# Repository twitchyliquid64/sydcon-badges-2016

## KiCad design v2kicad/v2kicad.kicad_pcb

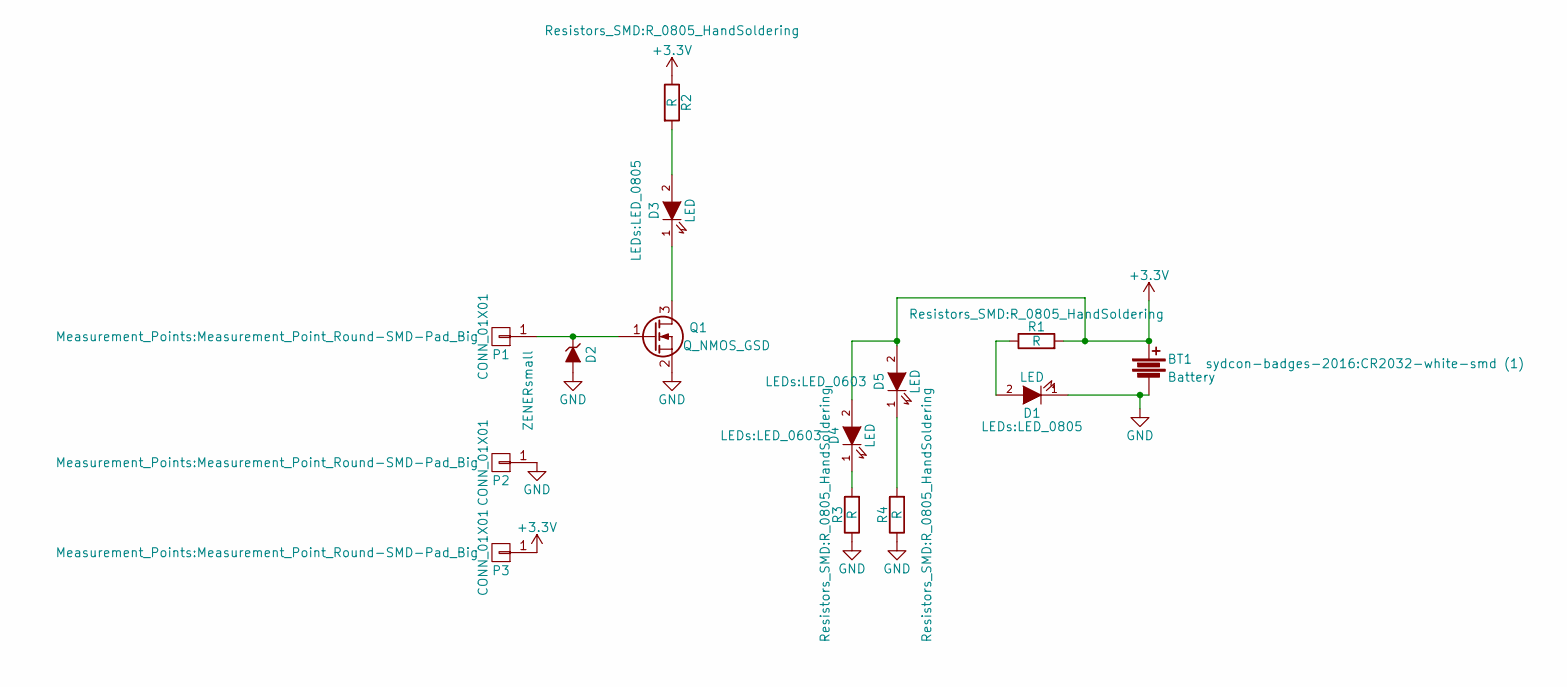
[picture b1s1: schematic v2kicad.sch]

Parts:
BT1: Battery; CR2032-white-smd (1)
D1, D3: LED; LED_0805
D2: ZENERsmall; SMA-SMB_Universal_Handsoldering
D4, D5: LED; LED_0603
P1, P2, P3: CONN_01X01; Measurement_Point_Round-SMD-Pad_Big
Q1: Q_NMOS_GSD; SOT-23_Handsoldering
R1, R2, R3, R4: R; R_0805_HandSoldering

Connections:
+3V3: BT1.1, D4.2 (A), D5.2 (A), P3.1, R1.2, R2.1
GND: BT1.2, D1.1 (K), D2.2 (A), P2.1, Q1.2 (S), R3.1, R4.1
unnamed: D1.2 (A), R1.1
unnamed: D2.1 (K), P1.1, Q1.1 (G)
unnamed: D3.1 (K), Q1.3 (D)
unnamed: D3.2 (A), R2.2
unnamed: D4.1 (K), R3.2
unnamed: D5.1 (K), R4.2

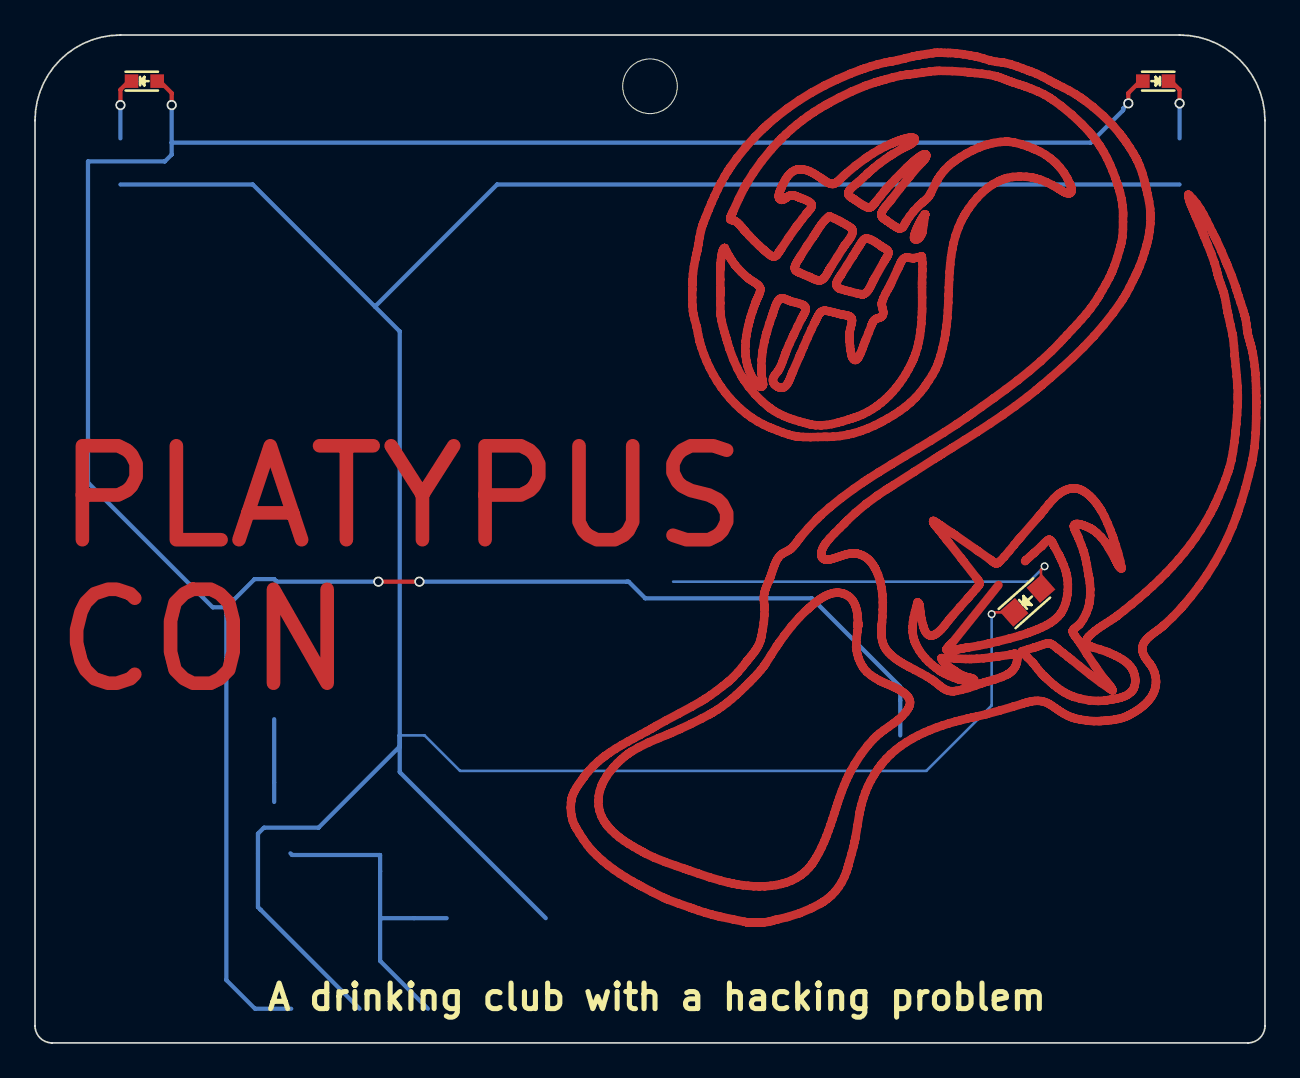
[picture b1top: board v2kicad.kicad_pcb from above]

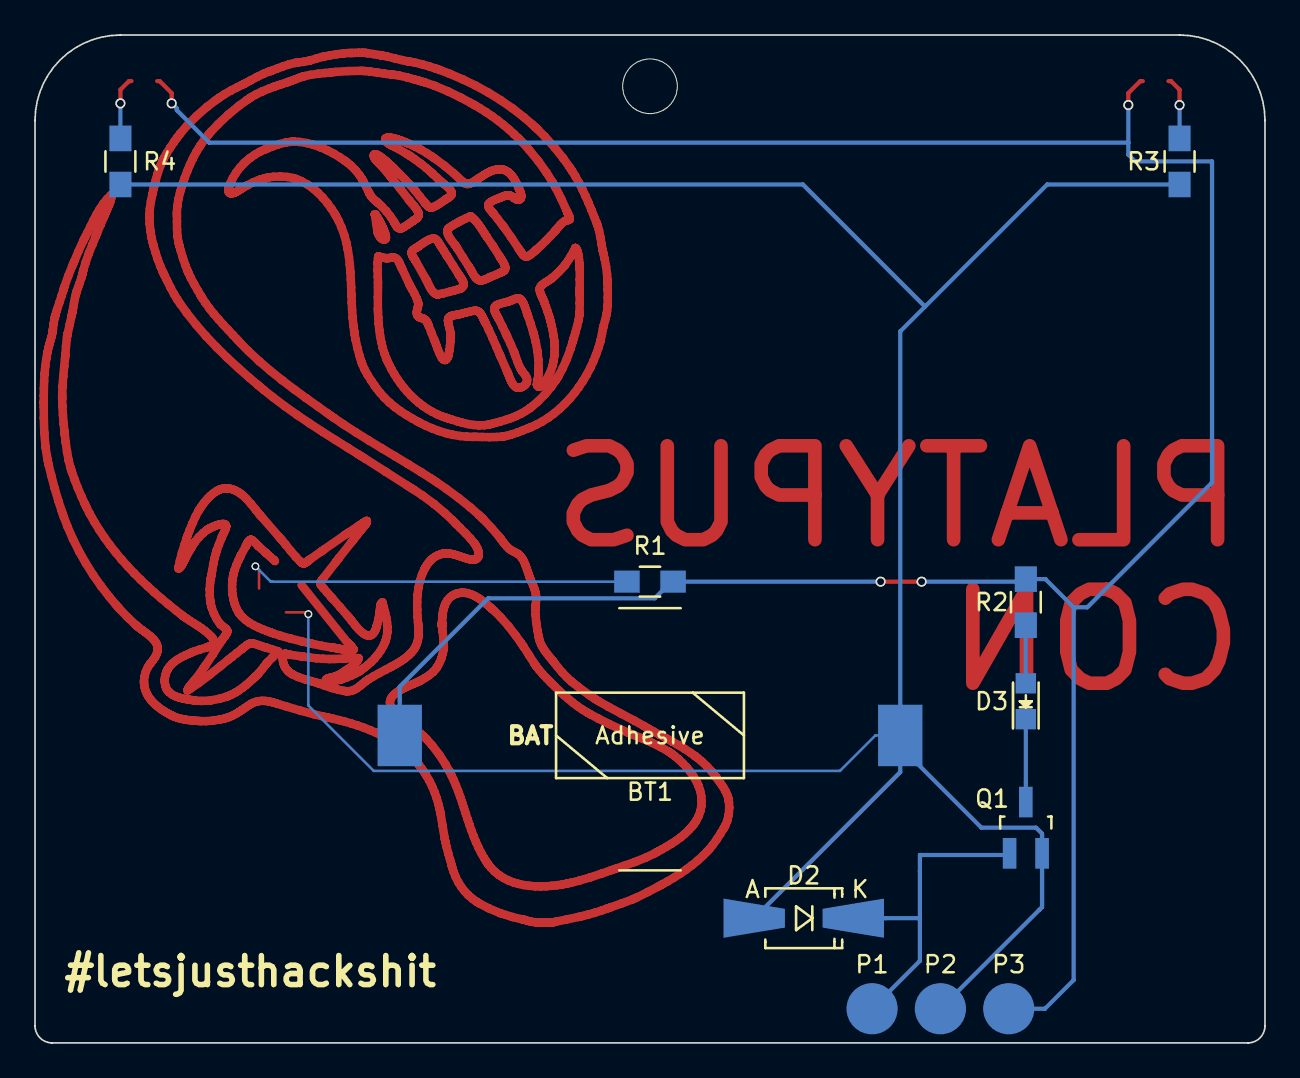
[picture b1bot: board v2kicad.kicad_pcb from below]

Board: 2 copper layers, 72.0 x 59.0 mm, 14 parts (11 on the bottom side), 8 nets.

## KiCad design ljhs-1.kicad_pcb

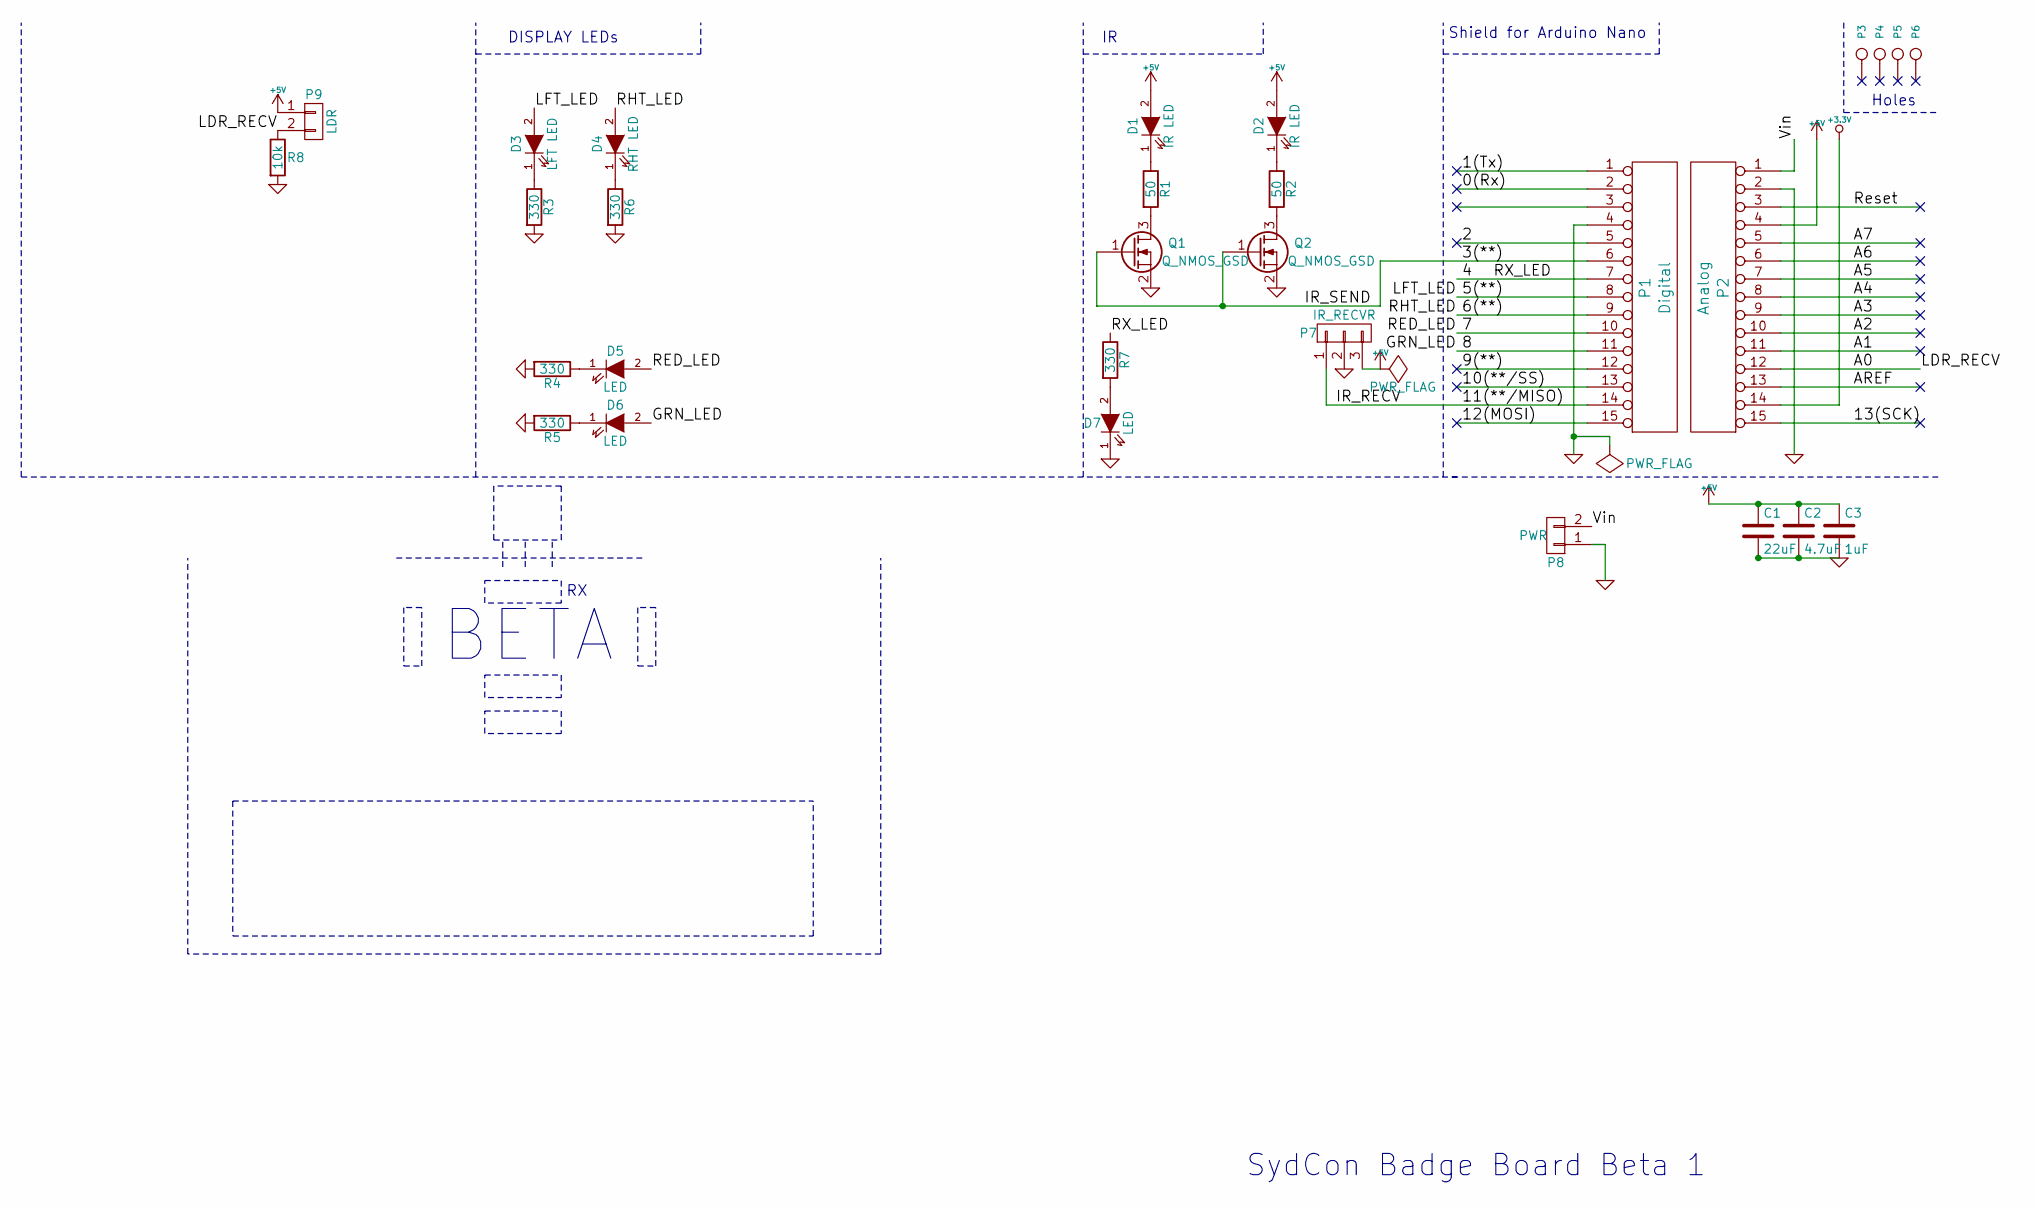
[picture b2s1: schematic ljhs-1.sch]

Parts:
C1: 22uF; C_0805_HandSoldering
C2: 4.7uF; C_0805_HandSoldering
C3: 1uF; C_0805_HandSoldering
D1, D2: IR LED; LED-3MM
D3: LFT LED; LED_0805
D4: RHT LED; LED_0805
D5, D6, D7: LED; LED_0805
P1: Digital; Socket_Strip_Arduino_1x15
P2: Analog; Socket_Strip_Arduino_1x15
P3, P4, P5, P6: CONN_1; 1pin_Nano
P7: IR_RECVR; Pin_Header_Straight_1x03
P8: PWR; Pin_Header_Straight_1x02
P9: LDR; Pin_Header_Straight_1x02
Q1, Q2: Q_NMOS_GSD; SOT-23_Handsoldering
R1, R2: 50; R_0805_HandSoldering
R3, R4, R5, R6, R7: 330; R_0805_HandSoldering
R8: 10k; R_0805_HandSoldering

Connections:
+3.3V: P2.14
+5V: C1.1, C2.1, C3.1, D1.2 (A), D2.2 (A), P2.4, P7.3, P9.1
/0(Rx): P1.2
/1(Tx): P1.1
/2: P1.5
/3(**): P1.6, Q1.1 (G), Q2.1 (G)
/4: P1.7, R7.1
/5(**): D3.2 (A), P1.8
/6(**): D4.2 (A), P1.9
/7: D5.2 (A), P1.10
/8: D6.2 (A), P1.11
/9(**): P1.12
/10(**/SS): P1.13
/11(**/MISO): P1.14, P7.1
/12(MOSI): P1.15 (p15)
/13(SCK): P2.15 (p15)
/A0: P2.12, P9.2, R8.1
/A1: P2.11
/A2: P2.10
/A3: P2.9
/A4: P2.8
/A5: P2.7
/A6: P2.6
/A7: P2.5
/AREF: P2.13
/Reset: P2.3
/Vin: P2.1, P8.2
GND: C1.2, C2.2, C3.2, D7.1 (K), P1.4, P2.2, P7.2, P8.1, Q1.2 (S), Q2.2 (S), R3.2, R4.2, R5.2, R6.2, R8.2
unnamed: D1.1 (K), R1.1
unnamed: D2.1 (K), R2.1
unnamed: D3.1 (K), R3.1
unnamed: D4.1 (K), R6.1
unnamed: D5.1 (K), R4.1
unnamed: D6.1 (K), R5.1
unnamed: D7.2 (A), R7.2
unnamed: Q1.3 (D), R1.2
unnamed: Q2.3 (D), R2.2

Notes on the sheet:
Holes
Shield for Arduino Nano
BETA
DISPLAY LEDs
SydCon Badge Board Beta 1

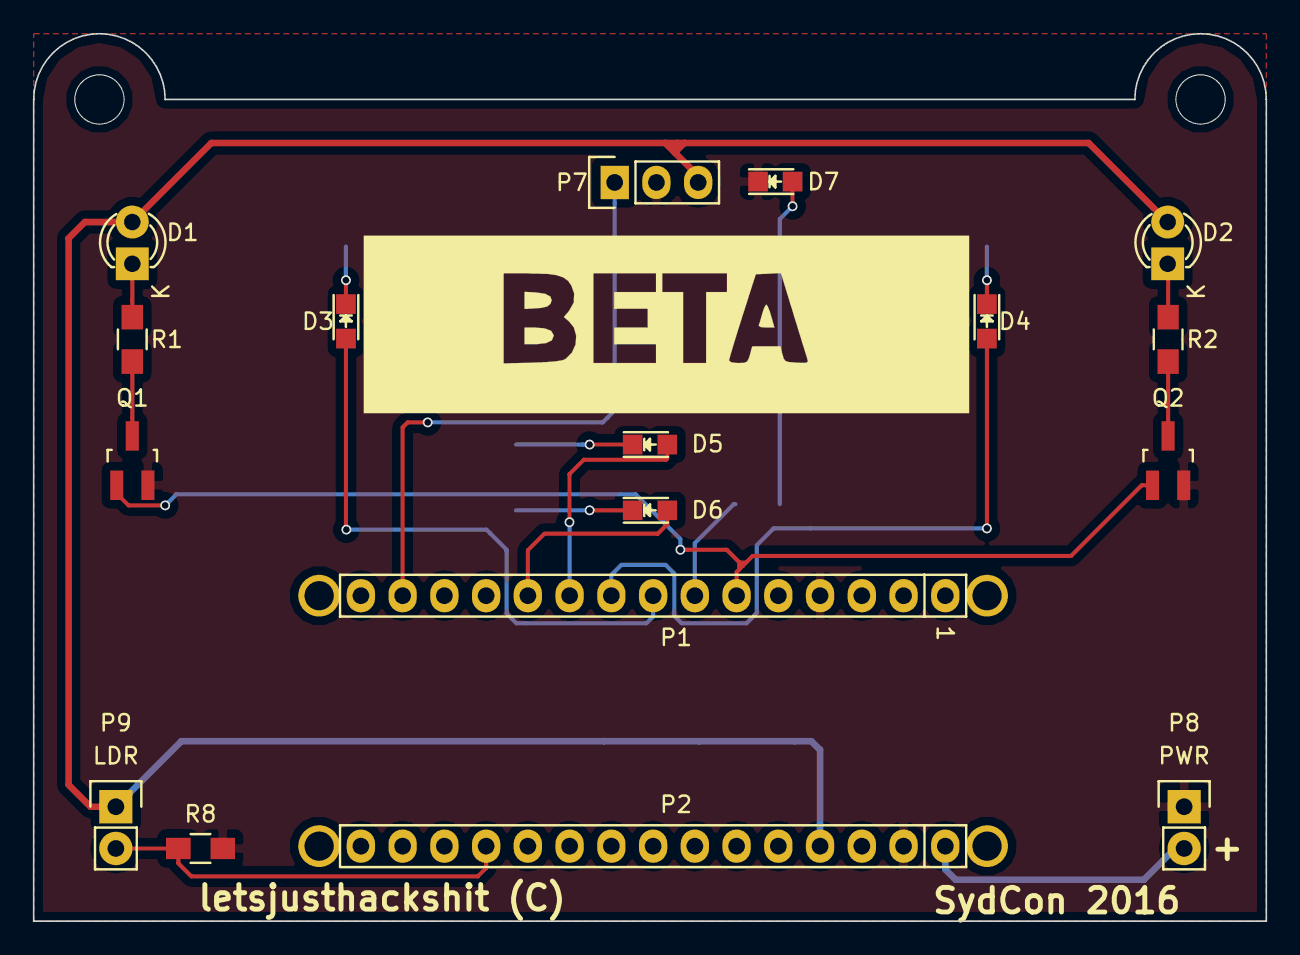
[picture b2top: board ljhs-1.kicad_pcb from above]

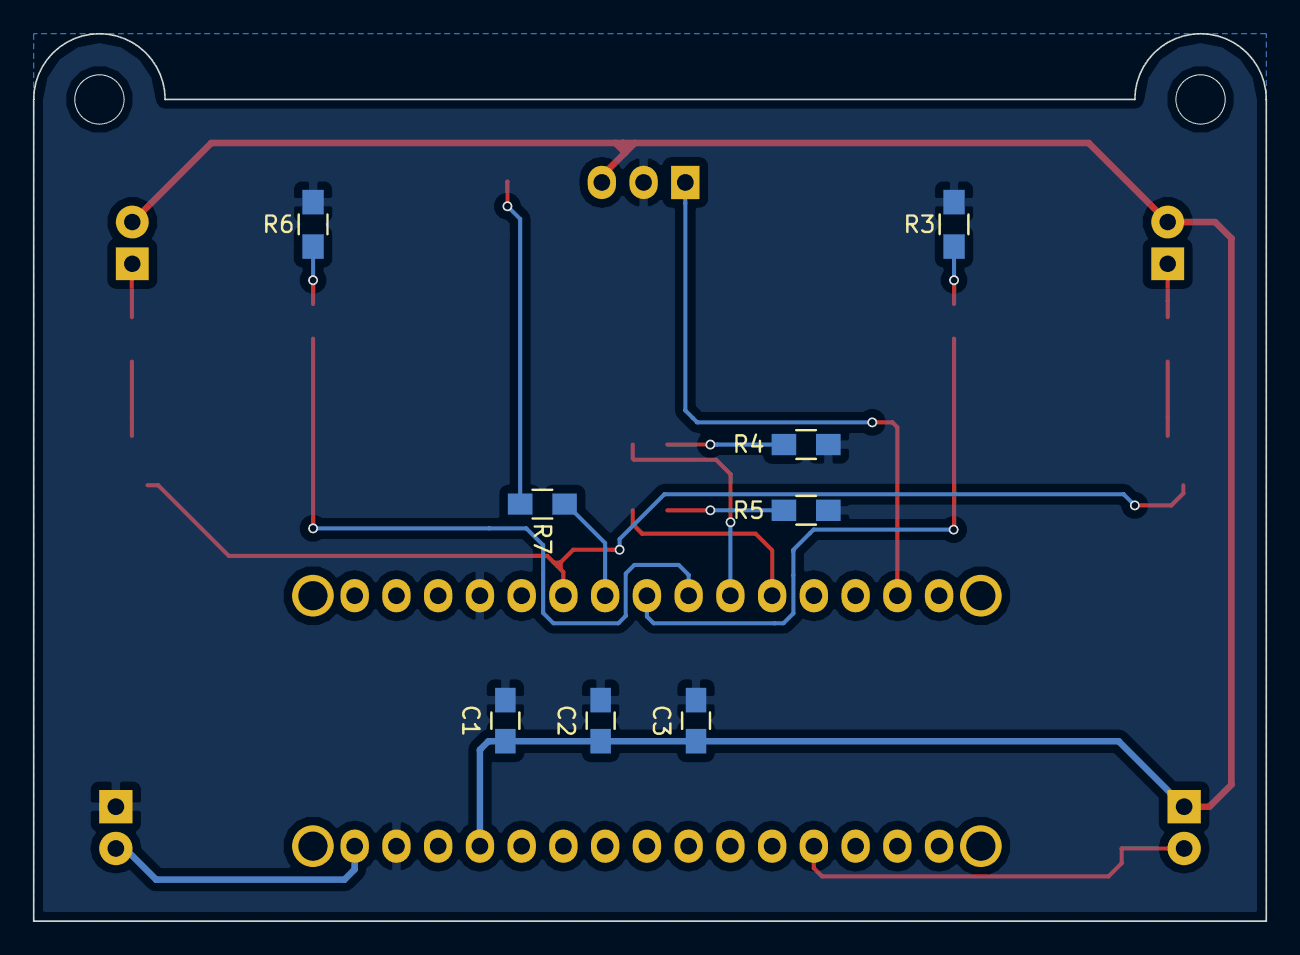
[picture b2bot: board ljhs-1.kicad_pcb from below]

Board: 2 copper layers, 75.0 x 54.0 mm, 29 parts (8 on the bottom side), 20 nets.

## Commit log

2016-03-25 Routing complete.
2016-08-20 New version - abandoning v1
2016-08-21 Progress
2016-08-21 Rewrite file to change platypus line width to 0.5mm
2016-08-27 Redone traces for main LED to avoid silkscreen
2016-08-27 Done script to translate platypus graphic to front copper
2016-08-27 final version with tiny vias - todo increase via size
2016-08-27 Changed vias to 0.3mm drill to save cost
